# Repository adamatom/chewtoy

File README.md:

# Chewtoy

This is a KiCad project for a i2c and GPIO expander cape for the BeagleBone
Black. It provides eight expansion ports, with each port offering access to the
common i2c bus as well as two dedicated GPIO pins

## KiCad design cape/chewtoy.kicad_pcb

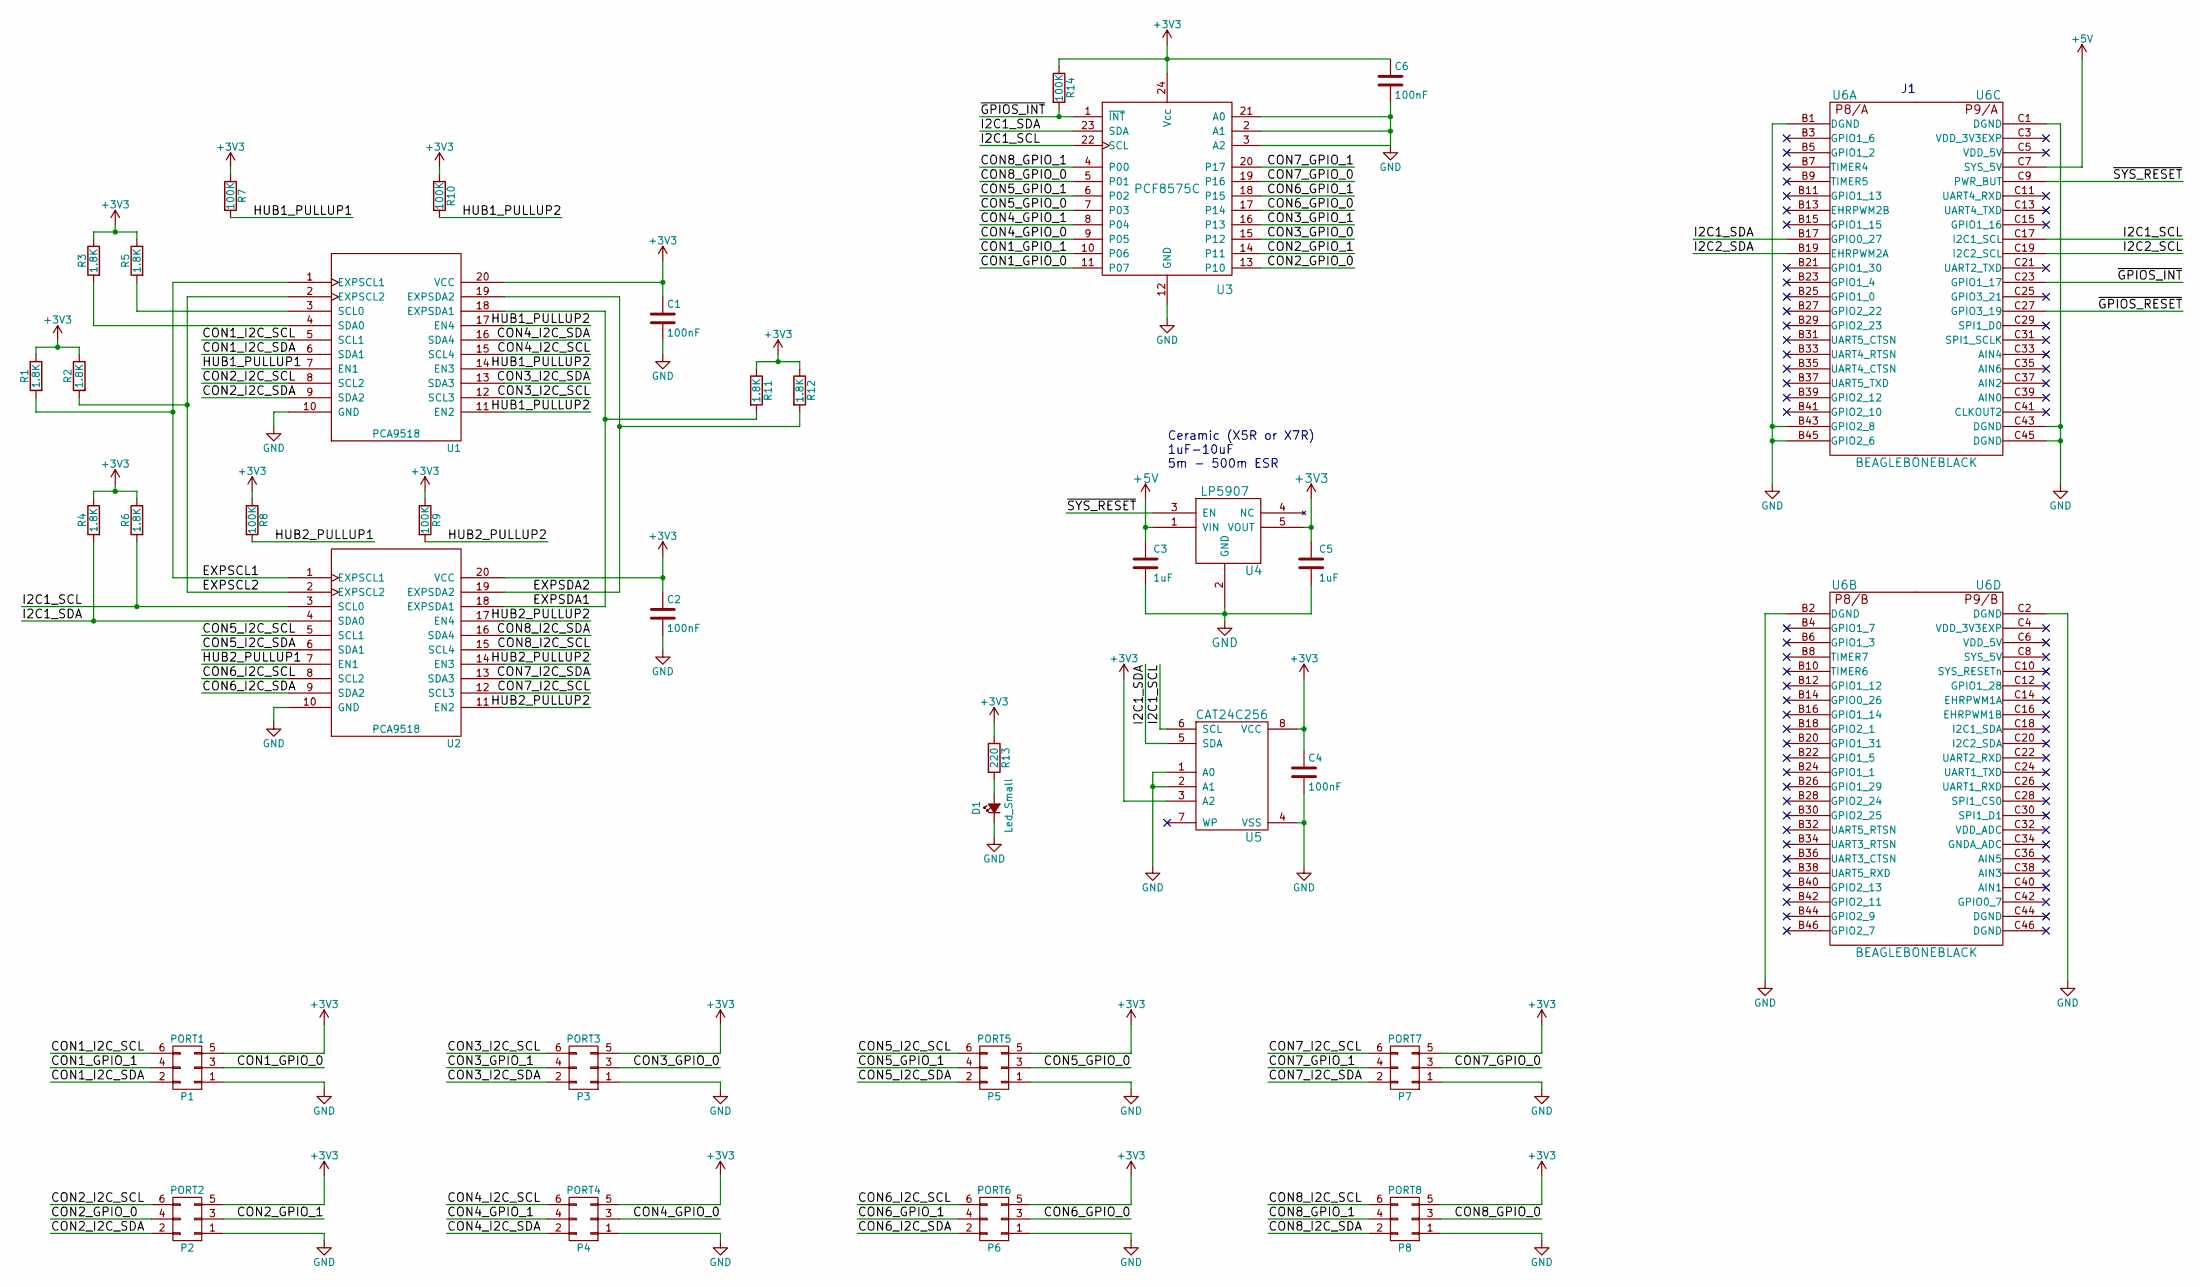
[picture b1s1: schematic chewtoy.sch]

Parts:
C1, C2, C4, C6: 100nF; C_0805
C3, C5: 1uF; C_0805
D1: Led_Small; C_0805
P1: PORT1; Pin_Header_Straight_2x03
P2: PORT2; Pin_Header_Straight_2x03
P3: PORT3; Pin_Header_Straight_2x03
P4: PORT4; Pin_Header_Straight_2x03
P5: PORT5; Pin_Header_Straight_2x03
P6: PORT6; Pin_Header_Straight_2x03
P7: PORT7; Pin_Header_Straight_2x03
P8: PORT8; Pin_Header_Straight_2x03
R1, R2, R3, R4, R5, R6, R11, R12: 1.8K; C_0805
R7, R8, R9, R10, R14: 100K; C_0805
R13: 220; C_0805
U1, U2: PCA9518; TSSOP-20_4.4x6.5mm_Pitch0.65mm
U3: PCF8575C; SOIC-24_7.5x15.4mm_Pitch1.27mm
U4: LP5907; SOT-23-5
U5: CAT24C256; SOIJ-8_5.3x5.3mm_Pitch1.27mm
U6: BEAGLEBONEBLACK

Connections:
+3V3: C1.1, C2.1, C4.1, C5.1, C6.1, P1.5, P2.5, P3.5, P4.5, P5.5, P6.5, P7.5, P8.5, R1.1, R2.1, R3.1, R4.1, R5.1, R6.1, R7.1, R8.1, R9.1, R10.1, R11.1, R12.1, R13.1, R14.1, U1.20 (VCC), U2.20 (VCC), U3.24 (Vcc), U4.5 (VOUT), U5.3 (A2), U5.8 (VCC)
+5V: C3.1, U4.1 (VIN), U6.C7 (SYS_5V)
/CON1_GPIO_0: P1.3, U3.11 (P07)
/CON1_GPIO_1: P1.4, U3.10 (P06)
/CON1_I2C_SCL: P1.6, U1.5 (SCL1)
/CON1_I2C_SDA: P1.2, U1.6 (SDA1)
/CON2_GPIO_0: P2.4, U3.13 (P10)
/CON2_GPIO_1: P2.3, U3.14 (P11)
/CON2_I2C_SCL: P2.6, U1.8 (SCL2)
/CON2_I2C_SDA: P2.2, U1.9 (SDA2)
/CON3_GPIO_0: P3.3, U3.15 (P12)
/CON3_GPIO_1: P3.4, U3.16 (P13)
/CON3_I2C_SCL: P3.6, U1.12 (SCL3)
/CON3_I2C_SDA: P3.2, U1.13 (SDA3)
/CON4_GPIO_0: P4.3, U3.9 (P05)
/CON4_GPIO_1: P4.4, U3.8 (P04)
/CON4_I2C_SCL: P4.6, U1.15 (SCL4)
/CON4_I2C_SDA: P4.2, U1.16 (SDA4)
/CON5_GPIO_0: P5.3, U3.7 (P03)
/CON5_GPIO_1: P5.4, U3.6 (P02)
/CON5_I2C_SCL: P5.6, U2.5 (SCL1)
/CON5_I2C_SDA: P5.2, U2.6 (SDA1)
/CON6_GPIO_0: P6.3, U3.17 (P14)
/CON6_GPIO_1: P6.4, U3.18 (P15)
/CON6_I2C_SCL: P6.6, U2.8 (SCL2)
/CON6_I2C_SDA: P6.2, U2.9 (SDA2)
/CON7_GPIO_0: P7.3, U3.19 (P16)
/CON7_GPIO_1: P7.4, U3.20 (P17)
/CON7_I2C_SCL: P7.6, U2.12 (SCL3)
/CON7_I2C_SDA: P7.2, U2.13 (SDA3)
/CON8_GPIO_0: P8.3, U3.5 (P01)
/CON8_GPIO_1: P8.4, U3.4 (P00)
/CON8_I2C_SCL: P8.6, U2.15 (SCL4)
/CON8_I2C_SDA: P8.2, U2.16 (SDA4)
/EXPSCL1: R1.2, U1.1 (EXPSCL1), U2.1 (EXPSCL1)
/EXPSCL2: R2.2, U1.2 (EXPSCL2), U2.2 (EXPSCL2)
/EXPSDA1: R11.2, U1.18 (EXPSDA1), U2.18 (EXPSDA1)
/EXPSDA2: R12.2, U1.19 (EXPSDA2), U2.19 (EXPSDA2)
/HUB1_PULLUP1: R7.2, U1.7 (EN1)
/HUB1_PULLUP2: R10.2, U1.11 (EN2), U1.14 (EN3), U1.17 (EN4)
/HUB2_PULLUP1: R8.2, U2.7 (EN1)
/HUB2_PULLUP2: R9.2, U2.11 (EN2), U2.14 (EN3), U2.17 (EN4)
/I2C1_SCL: R6.2, U2.3 (SCL0), U3.22 (SCL), U5.6 (SCL), U6.C17 (I2C1_SCL)
/I2C1_SDA: R4.2, U2.4 (SDA0), U3.23 (SDA), U5.5 (SDA), U6.B17 (GPIO0_27)
/I2C2_SCL: U6.C19 (I2C2_SCL)
/I2C2_SDA: U6.B19 (EHRPWM2A)
/~GPIOS_INT: R14.2, U3.1 (~INT), U6.C23 (GPIO1_17)
/~GPIOS_RESET: U6.C27 (GPIO3_19)
/~SYS_RESET: U4.3 (EN), U6.C9 (PWR_BUT)
GND: C1.2, C2.2, C3.2, C4.2, C5.2, C6.2, D1.1 (K), P1.1, P2.1, P3.1, P4.1, P5.1, P6.1, P7.1, P8.1, U1.10 (GND), U2.10 (GND), U3.2 (A1), U3.3 (A2), U3.12 (GND), U3.21 (A0), U4.2 (GND), U5.1 (A0), U5.2 (A1), U5.4 (VSS), U6.B1 (DGND), U6.B2 (DGND), U6.B43 (GPIO2_8), U6.B45 (GPIO2_6), U6.C1 (DGND), U6.C2 (DGND), U6.C43 (DGND), U6.C45 (DGND)
unnamed: D1.2 (A), R13.2
unnamed: R3.2, U1.4 (SDA0)
unnamed: R5.2, U1.3 (SCL0)

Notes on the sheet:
Ceramic (X5R or X7R) 1uF-10uF 5m - 500m ESR

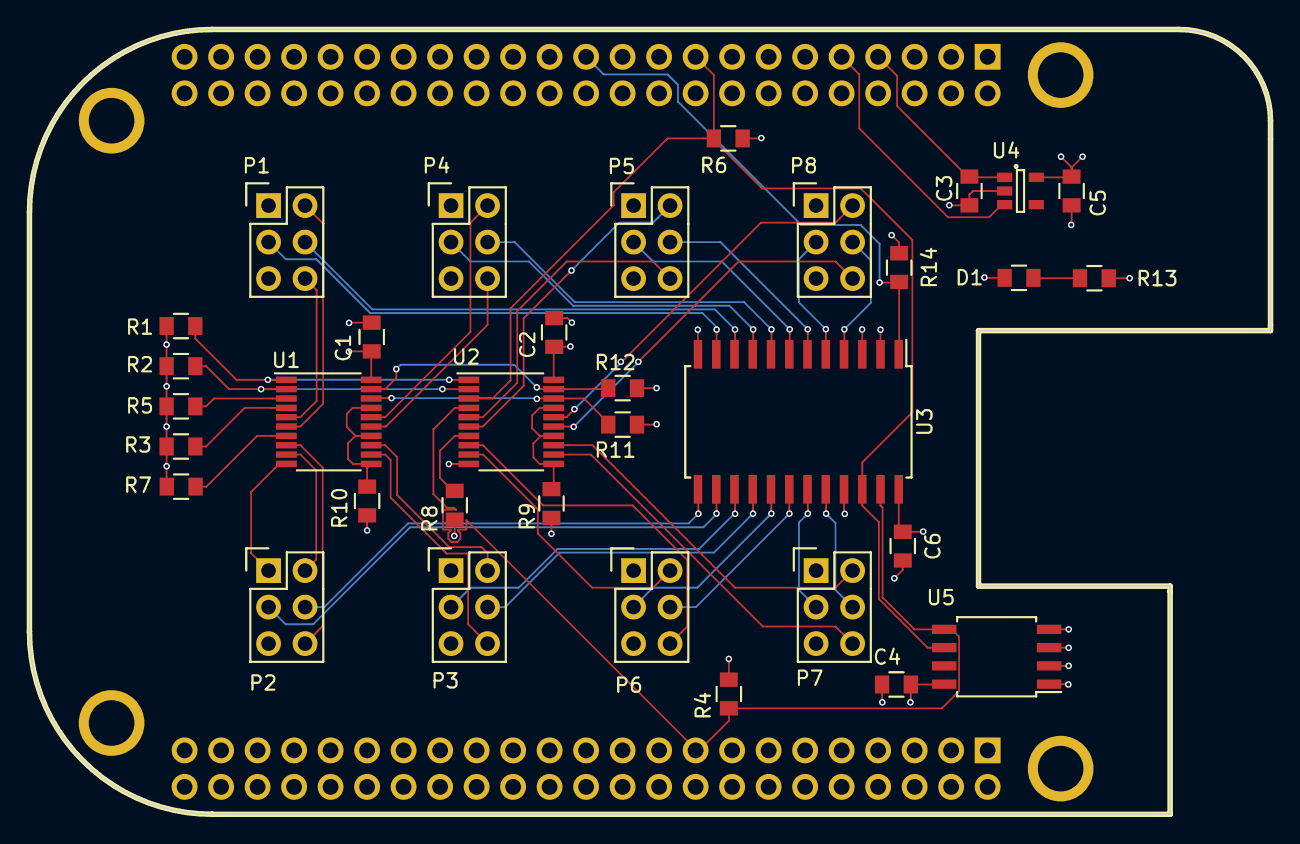
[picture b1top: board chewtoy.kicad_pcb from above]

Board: 4 copper layers, 86.4 x 54.6 mm, 35 parts (0 on the bottom side), 50 nets.

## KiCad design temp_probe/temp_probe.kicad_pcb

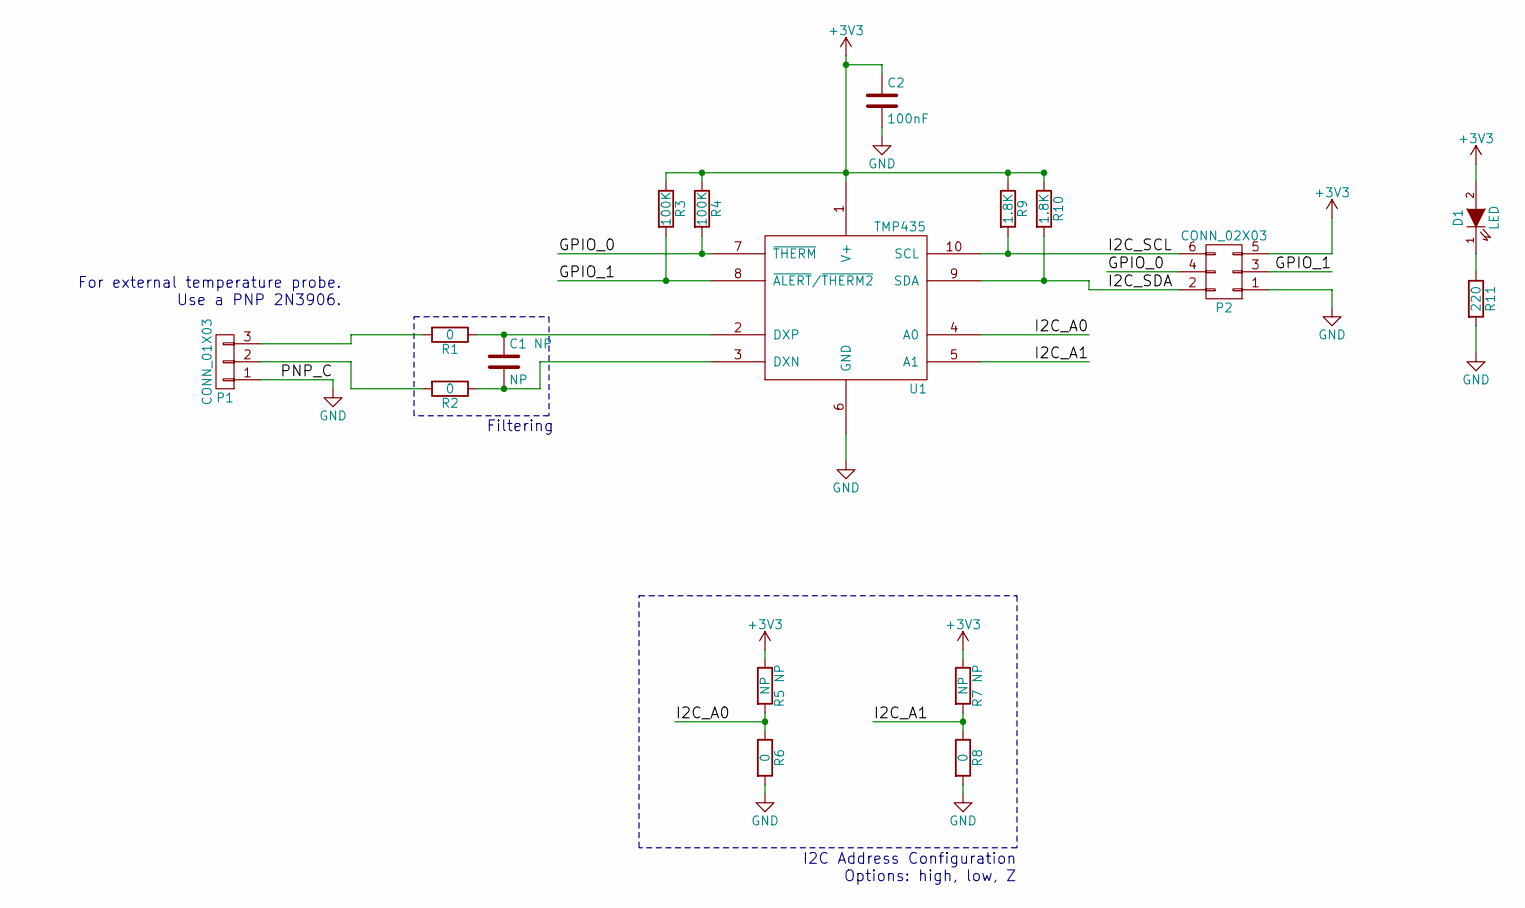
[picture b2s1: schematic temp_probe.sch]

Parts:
C1: NP; C_0805
C2: 100nF; C_0805
D1: LED; LED-0805
P1: CONN_01X03; Socket_Strip_Angled_1x03
P2: CONN_02X03; Socket_Strip_Angled_2x03
R1, R2, R6, R8: 0; R_0805
R3, R4: 100K; R_0805
R5, R7: NP; R_0805
R9, R10: 1.8K; R_0805
R11: 220; R_0805
U1: TMP435; MSOP-10-1EP_3x3mm_Pitch0.5mm

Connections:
+3V3: C2.1, D1.2 (A), P2.5, R3.1, R4.1, R5.1, R7.1, R9.1, R10.1, U1.1 (V+)
/GPIO_0: P2.4, R4.2, U1.7 (~THERM)
/GPIO_1: P2.3, R3.2, U1.8 (~ALERT~/~THERM2~)
/I2C_A0: R5.2, R6.1, U1.4 (A0)
/I2C_A1: R7.2, R8.1, U1.5 (A1)
/I2C_SCL: P2.6, R9.2, U1.10 (SCL)
/I2C_SDA: P2.2, R10.2, U1.9 (SDA)
GND: C2.2, P1.1, P2.1, R6.2, R8.2, R11.2, U1.6 (GND)
unnamed: C1.1, R1.1, U1.2 (DXP)
unnamed: C1.2, R2.1, U1.3 (DXN)
unnamed: D1.1 (K), R11.1
unnamed: P1.2, R2.2
unnamed: P1.3, R1.2

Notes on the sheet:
For external temperature probe. Use a PNP 2N3906.
Filtering
I2C Address Configuration Options: high, low, Z

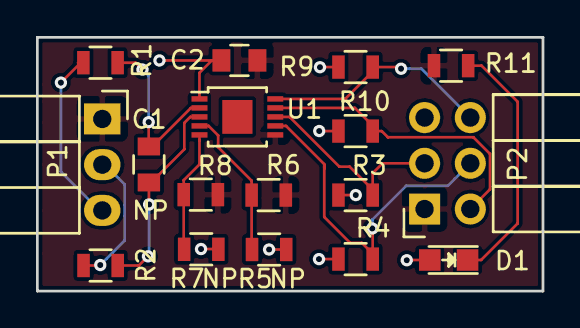
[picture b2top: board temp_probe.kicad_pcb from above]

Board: 2 copper layers, 28.1 x 14.1 mm, 17 parts (0 on the bottom side), 13 nets.

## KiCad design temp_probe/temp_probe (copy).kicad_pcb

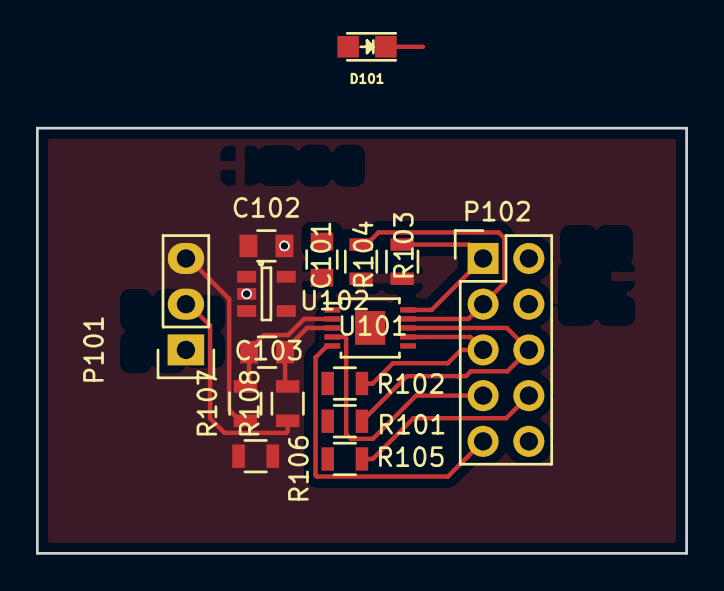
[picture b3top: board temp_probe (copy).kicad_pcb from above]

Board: 2 copper layers, 36.1 x 23.6 mm, 16 parts (0 on the bottom side), 14 nets.

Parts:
C101: 100nF; C_0805
C102: 4.7uF; C_0805
C103: NP; C_0805
D101: LED; LED-0805
P101: CONN_01X03; Socket_Strip_Straight_1x03
P102: CONN_02X05; Pin_Header_Straight_2x05
R101, R102, R105: 100K; R_0805
R103, R104: 1.8K; R_0805
R106: 220; R_0805
R107, R108: 0; R_0805
U101: TMP435; MSOP-10-1EP_3x3mm_Pitch0.5mm
U102: TPS73233; SOT-23-5

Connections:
+3V3: C101.1, D101.2, R101.1, R102.1, R103.1, R104.1, U101.1, U102.5
+5V: C102.1, P102.2, U102.1
/GPIO_0: P102.5, R102.2, U101.7
/GPIO_1: P102.6, R101.2, U101.8
/I2C_A0: P102.7, U101.4
/I2C_A1: P102.9, U101.5
/I2C_SCL: P102.1, R103.2, U101.10
/I2C_SDA: P102.3, R104.2, U101.9
/PNP_B: C103.2, P101.2, R108.1, R108.2, U101.3
/PNP_E: C103.1, P101.3, R107.1, R107.2, U101.2
/PRB_CAT: P102.8, R105.2
/PRB_EN: P102.4, U102.3
GND: C101.2, C102.2, P101.1, P102.10, R105.1, R106.2, U101.6, U102.2
unnamed: D101.1, R106.1

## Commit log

2021-12-01 Add README
